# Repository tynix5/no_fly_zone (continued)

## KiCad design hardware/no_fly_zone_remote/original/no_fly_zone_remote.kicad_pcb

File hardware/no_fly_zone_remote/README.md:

# no_fly_zone_remote Schematic + PCB
## Overview

In order to effectively control the quadcopter, the wireless remote control requires several components...

### Microcontroller
The STM32L432KC microcontroller was chosen for its small package, low power draw, and adequate maximum clock speed.
### Control Inputs - Joysticks, Encoders
The joysticks, PS5 TMR (Tunnel Magnetoresistance), were chosen due to their low deadzones, small footprint, and wide availability. The joysticks control the quadcopters throttle, yaw, pitch, and roll. The encoder included on the PCB is used to switch between various menus, displayed on the SSD1306 OLED, and for tuning quadcopter PID parameters easily. 
### Wireless Communication
The nRF24L01 radio was chosen for its availablity and simplicity. For additional improvements, an PA + LNA combo can be added to extend range.
### Charging Circuitry
The charging circuity involves an autoswitching power multiplexer and a linear 1S LiPo charger. The autoswitcher IC automatically chooses the highest available power source. If only LiPo is connected, it is used to power the remote, but if LiPo and USB power are present, USB power is used to power the board and simultaneously charge the LiPo. The board can also be powered using only USB without a LiPo.
### OLED
Displays all relevant information: battery percentages (for both remote and quadcopter), joystick deadzones, PID parameters. Page switches via encoder.
\
\
\
More details are given on the schematics for exact component parameters.\
All footprints and schematics symbols were found online or in KiCAD libraries.

## Versions
The folder structure indicates there are two versions of the PCB: original and revised. The original PCB was never manufactured and used the wrong footprints for several parts, as well as did not have great PCB design characteristics. Instead, the revised version was manufactured and shows all correct footprints and better PCB design methodology. 

An important note on the revised version is Revision 1.0 used the wrong TVS diodes for USB D+ and D-, but these were changed to dedicated USB TVS diodes in a later revision.

## Schematics

### Hierarchal Schematic
The hierarchal schematic details how the MCU, sensors, and power schematics are connected.
<p align="center">
  <br>
</p>

### MCU
<p align="center">
  <br>
</p>

### Sensors (Radio, OLED, Joysticks, Encoder)
<p align="center">
  <br>
</p>

### Misc
Contains four M3 screws with pads, not shown for brevity

### PCB
Note on radio layout: the nRF24L01 is surrounded by a continuous ground plane on the top layer as well as the layer directly underneath the antenna for stability. Stitching vias are placed about ~6mm apart (between lambda/10 - lambda/20 of 2.4 GHz wavelength) near antenna for shielding.
<p align="center">
  <br>
</p>

### 3D Model

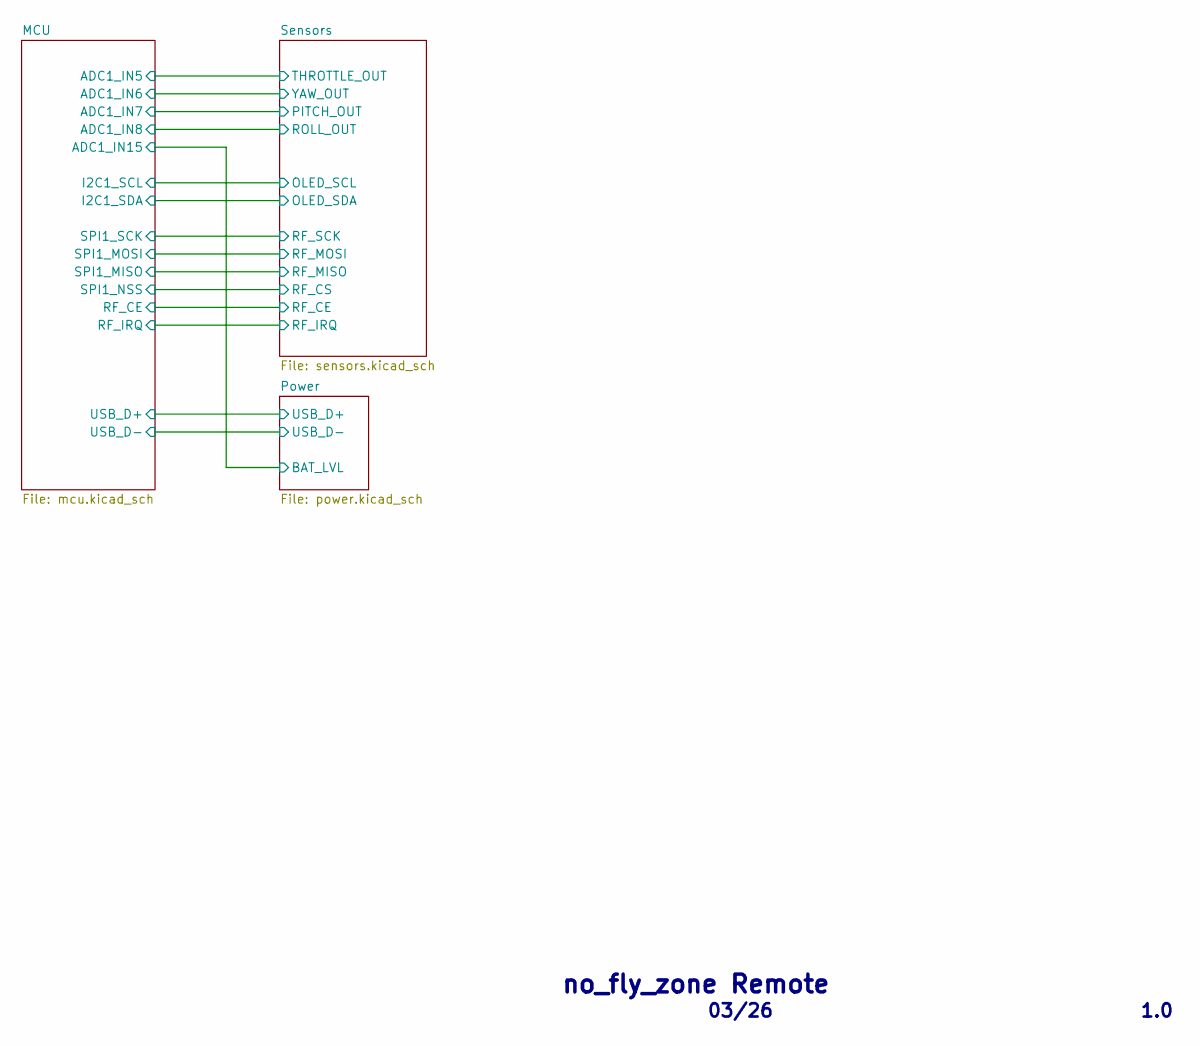
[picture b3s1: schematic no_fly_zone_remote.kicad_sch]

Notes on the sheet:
no_fly_zone Remote
03/26
1.0

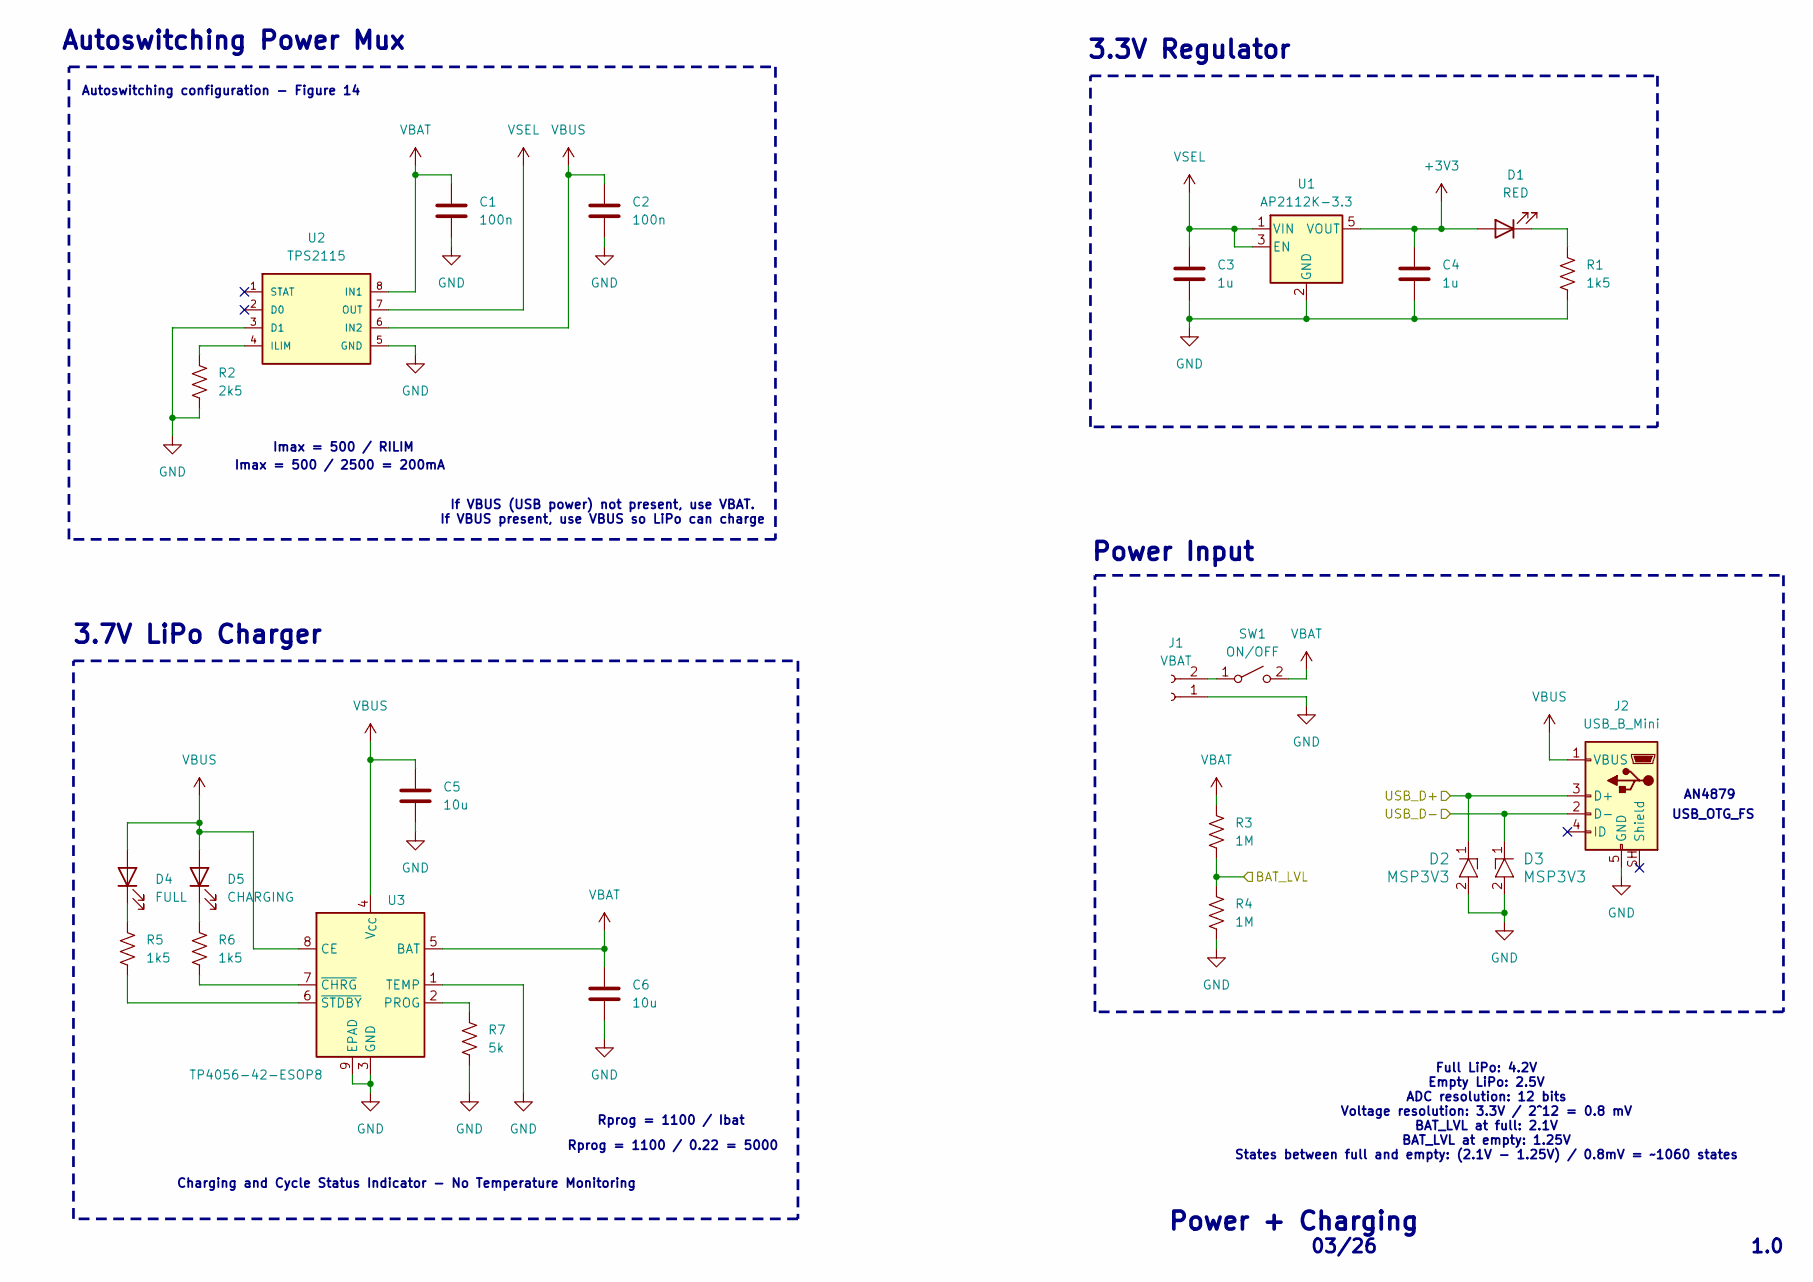
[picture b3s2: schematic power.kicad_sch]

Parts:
C1, C2: 100n; C_0805_2012Metric
C3, C4: 1u; C_0805_2012Metric
C5, C6: 10u; C_0805_2012Metric
D1: RED; LED_0805_2012Metric
D2, D3: MSP3V3; DO-219AD_VIS
D4: FULL; LED_0805_2012Metric
D5: CHARGING; LED_0805_2012Metric
J1: VBAT; JST_PH_S2B-PH-K_1x02_P2.00mm_Horizontal
J2: USB_B_Mini; EDAC_690-005-299-043
R1, R5, R6: 1k5; R_0805_2012Metric
R2: 2k5; R_0805_2012Metric
R3, R4: 1M; R_0805_2012Metric
R7: 5k; R_0805_2012Metric
SW1: ON/OFF; PinHeader_1x02_P2.54mm_Vertical
U1: AP2112K-3.3; SOT-23-5
U2: TPS2115; TPS2115A-TSSOP-8
U3: TP4056-42-ESOP8; SOIC-8-1EP_3.9x4.9mm_P1.27mm_EP2.41x3.3mm

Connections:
+3V3: C4.1, D1.2 (A), U1.5 (VOUT); also elsewhere on the board
/MCU/ADC1_IN15: R3.2, R4.1; also elsewhere on the board
/MCU/USB_D+: D2.1, J2.3 (D+); also elsewhere on the board
/MCU/USB_D-: D3.1, J2.2 (D-); also elsewhere on the board
GND: C1.2, C2.2, C3.2, C4.2, C5.2, C6.2, D2.2, D3.2, J1.1, J2.5 (GND), R1.2, R2.2, R4.2, R7.2, U1.2 (GND), U2.3 (D1), U2.5 (GND), U3.1 (TEMP), U3.3 (GND), U3.9 (EPAD); also elsewhere on the board
unnamed: D1.1 (K), R1.1
unnamed: D4.1 (K), R5.1
unnamed: D5.1 (K), R6.1
unnamed: J1.2, SW1.1 (A)
unnamed: R2.1, U2.4 (ILIM)
unnamed: R7.1, U3.2 (PROG)
unnamed: R6.2, U3.7 (~CHRG)
unnamed: R5.2, U3.6 (~STDBY)
VBAT: C1.1, C6.1, R3.1, SW1.2 (B), U2.8 (IN1), U3.5 (BAT)
VBUS: C2.1, C5.1, D4.2 (A), D5.2 (A), J2.1 (VBUS), U2.6 (IN2), U3.4 (V_{CC}), U3.8 (CE)
VSEL: C3.1, U1.1 (VIN), U1.3 (EN), U2.7 (OUT)

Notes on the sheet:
Power + Charging
Power Input
3.3V Regulator
Rprog = 1100 / 0.22 = 5000
Imax = 500 / 2500 = 200mA
1.0
Rprog = 1100 / Ibat
Imax = 500 / RILIM
Autoswitching Power Mux
If VBUS (USB power) not present, use VBAT. If VBUS present, use VBUS so LiPo can charge
03/26
Autoswitching configuration - Figure 14
3.7V LiPo Charger
Charging and Cycle Status Indicator - No Temperature Monitoring
USB_OTG_FS
AN4879
Full LiPo: 4.2V Empty LiPo: 2.5V ADC resolution: 12 bits Voltage resolution: 3.3V / 2^12 = 0.8 mV BAT_LVL at full: 2.1V BAT_LVL at empty: 1.25V States between full and empty: (2.1V - 1.25V) / 0.8mV = ~1060 states

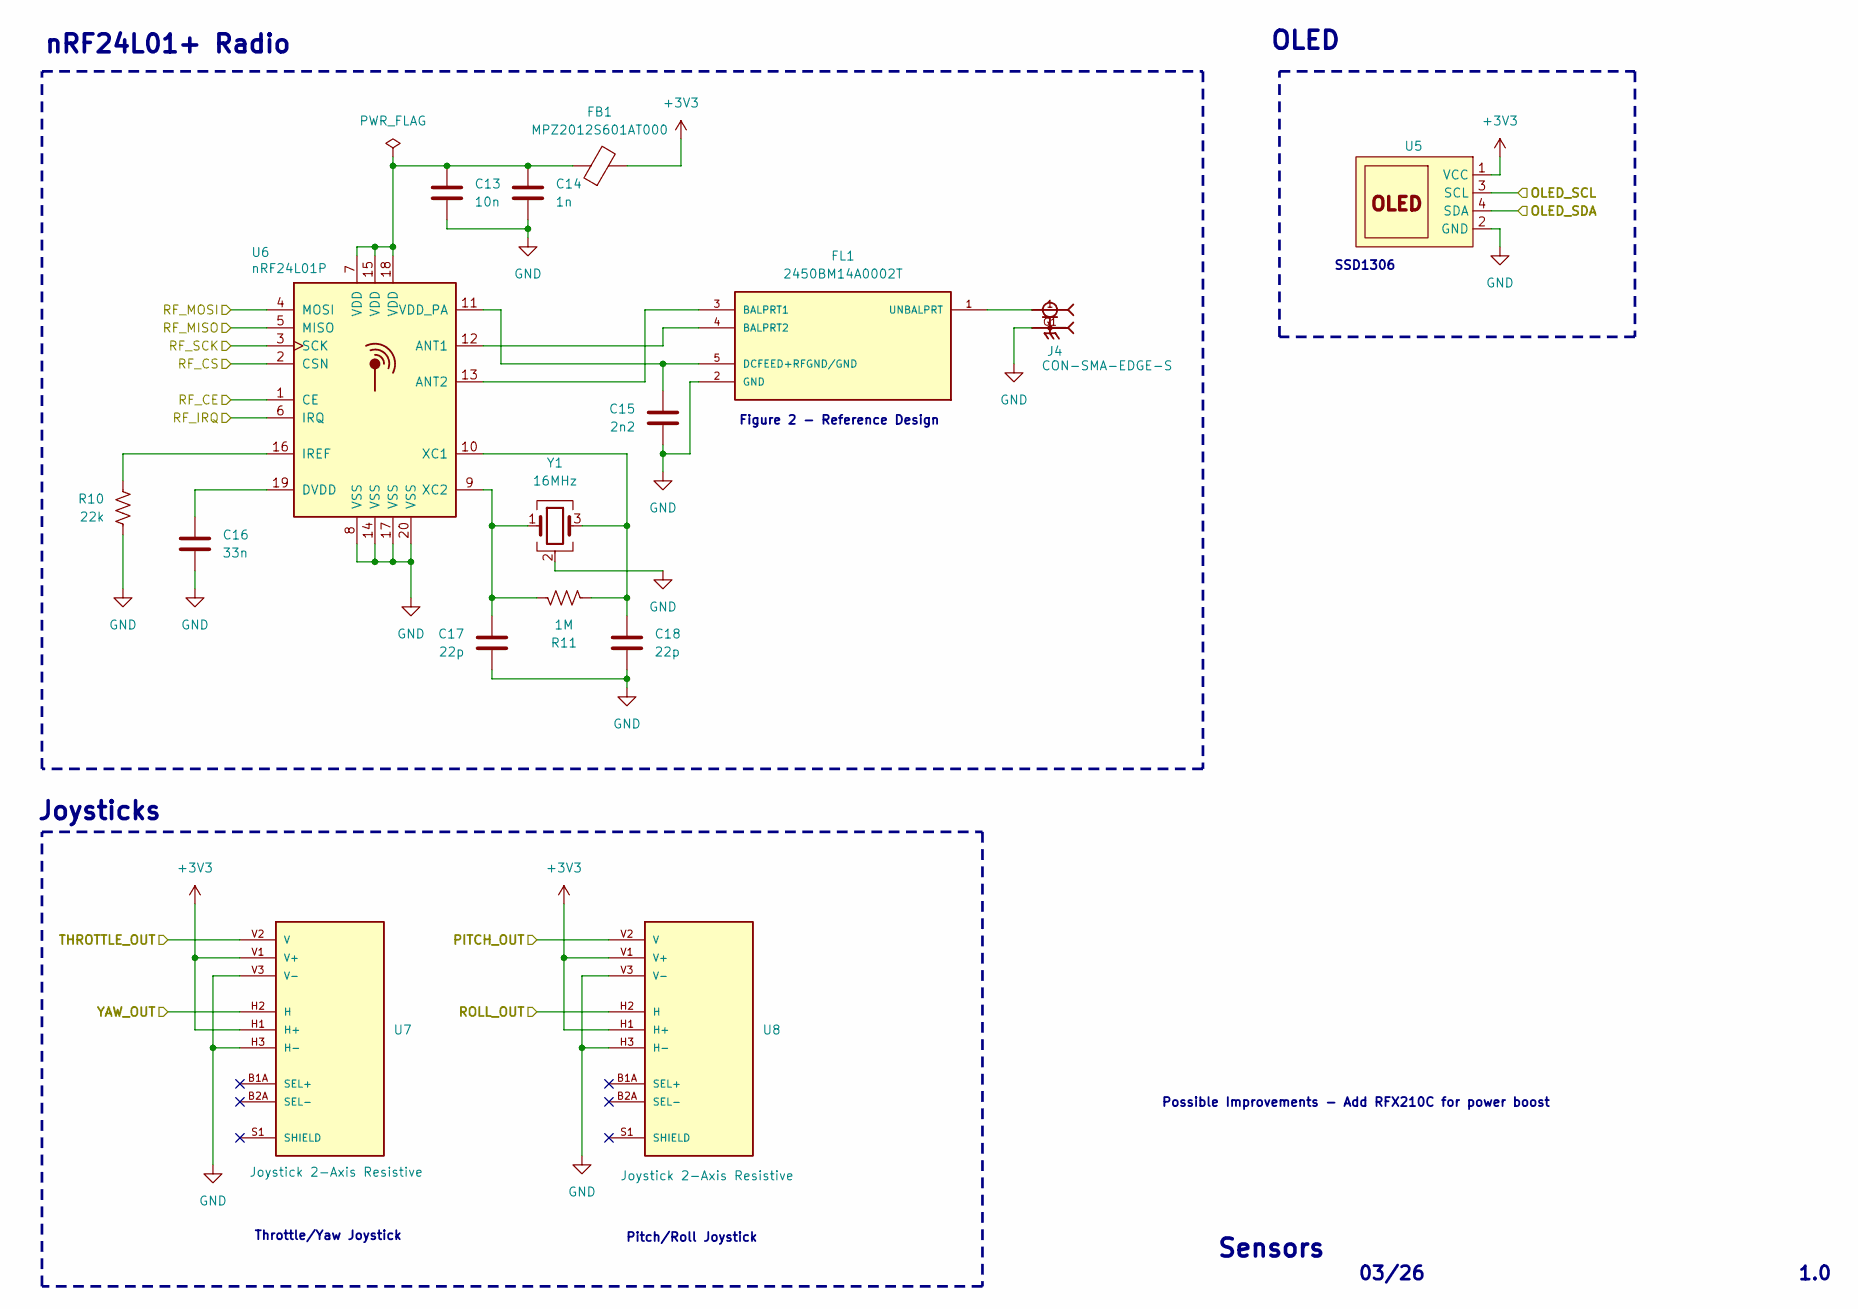
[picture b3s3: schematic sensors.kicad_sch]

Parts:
C13: 10n; C_0402_1005Metric
C14: 1n; C_0402_1005Metric
C15: 2n2; C_0402_1005Metric
C16: 33n; C_0402_1005Metric
C17, C18: 22p; C_0402_1005Metric
FB1: MPZ2012S601AT000; R_0805_2012Metric
FL1: 2450BM14A0002T; FIL_2450BM14A0002T
J4: CON-SMA-EDGE-S; RFSOLUTIONS_CON-SMA-EDGE-S
R10: 22k; R_0402_1005Metric
R11: 1M; R_0402_1005Metric
U5: PinHeader_1x04_P2.54mm_Vertical
U6: nRF24L01P; QFN-20-1EP_4x4mm_P0.5mm_EP2.5x2.5mm
U7, U8: Joystick 2-Axis Resistive; XDCR_COM-09032
Y1: 16MHz; XTAL_ABM8AIG-16.000MHZ-12-2Z-T3

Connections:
+3V3: FB1.2, U5.1 (VCC), U7.H1 (H+), U7.V1 (V+), U8.H1 (H+), U8.V1 (V+); also elsewhere on the board
/MCU/ADC1_IN5: U7.V2 (V); also elsewhere on the board
/MCU/ADC1_IN6: U7.H2 (H); also elsewhere on the board
/MCU/ADC1_IN7: U8.V2 (V); also elsewhere on the board
/MCU/ADC1_IN8: U8.H2 (H); also elsewhere on the board
/MCU/I2C1_SCL: U5.3 (SCL); also elsewhere on the board
/MCU/I2C1_SDA: U5.4 (SDA); also elsewhere on the board
/MCU/RF_CE: U6.1 (CE); also elsewhere on the board
/MCU/RF_IRQ: U6.6 (IRQ); also elsewhere on the board
/MCU/SPI1_MISO: U6.5 (MISO); also elsewhere on the board
/MCU/SPI1_MOSI: U6.4 (MOSI); also elsewhere on the board
/MCU/SPI1_NSS: U6.2 (CSN); also elsewhere on the board
/MCU/SPI1_SCK: U6.3 (SCK); also elsewhere on the board
GND: C13.2, C14.2, C15.2, C16.2, C17.2, C18.2, FL1.2 (GND), J4.G1, J4.G2, J4.G3, J4.G4, R10.2, U5.2 (GND), U6.8 (VSS), U6.14 (VSS), U6.17 (VSS), U6.20 (VSS), U7.H3 (H-), U7.V3 (V-), U8.H3 (H-), U8.V3 (V-), Y1.2 (G), Y1.4 (G); also elsewhere on the board
unnamed: C13.1, C14.1, FB1.1, U6.7 (VDD), U6.15 (VDD), U6.18 (VDD)
unnamed: FL1.3 (BALPRT1), U6.13 (ANT2)
unnamed: FL1.4 (BALPRT2), U6.12 (ANT1)
unnamed: C15.1, FL1.5 (DCFEED+RFGND/GND), U6.11 (VDD_PA)
unnamed: FL1.1 (UNBALPRT), J4.1
unnamed: C16.1, U6.19 (DVDD)
unnamed: R10.1, U6.16 (IREF)
unnamed: C18.1, R11.1, U6.10 (XC1), Y1.3
unnamed: C17.1, R11.2, U6.9 (XC2), Y1.1

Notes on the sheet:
03/26
Figure 2 - Reference Design
nRF24L01+ Radio
SSD1306
Joysticks
OLED
1.0
Sensors
Throttle/Yaw Joystick
Pitch/Roll Joystick
Possible Improvements - Add RFX210C for power boost

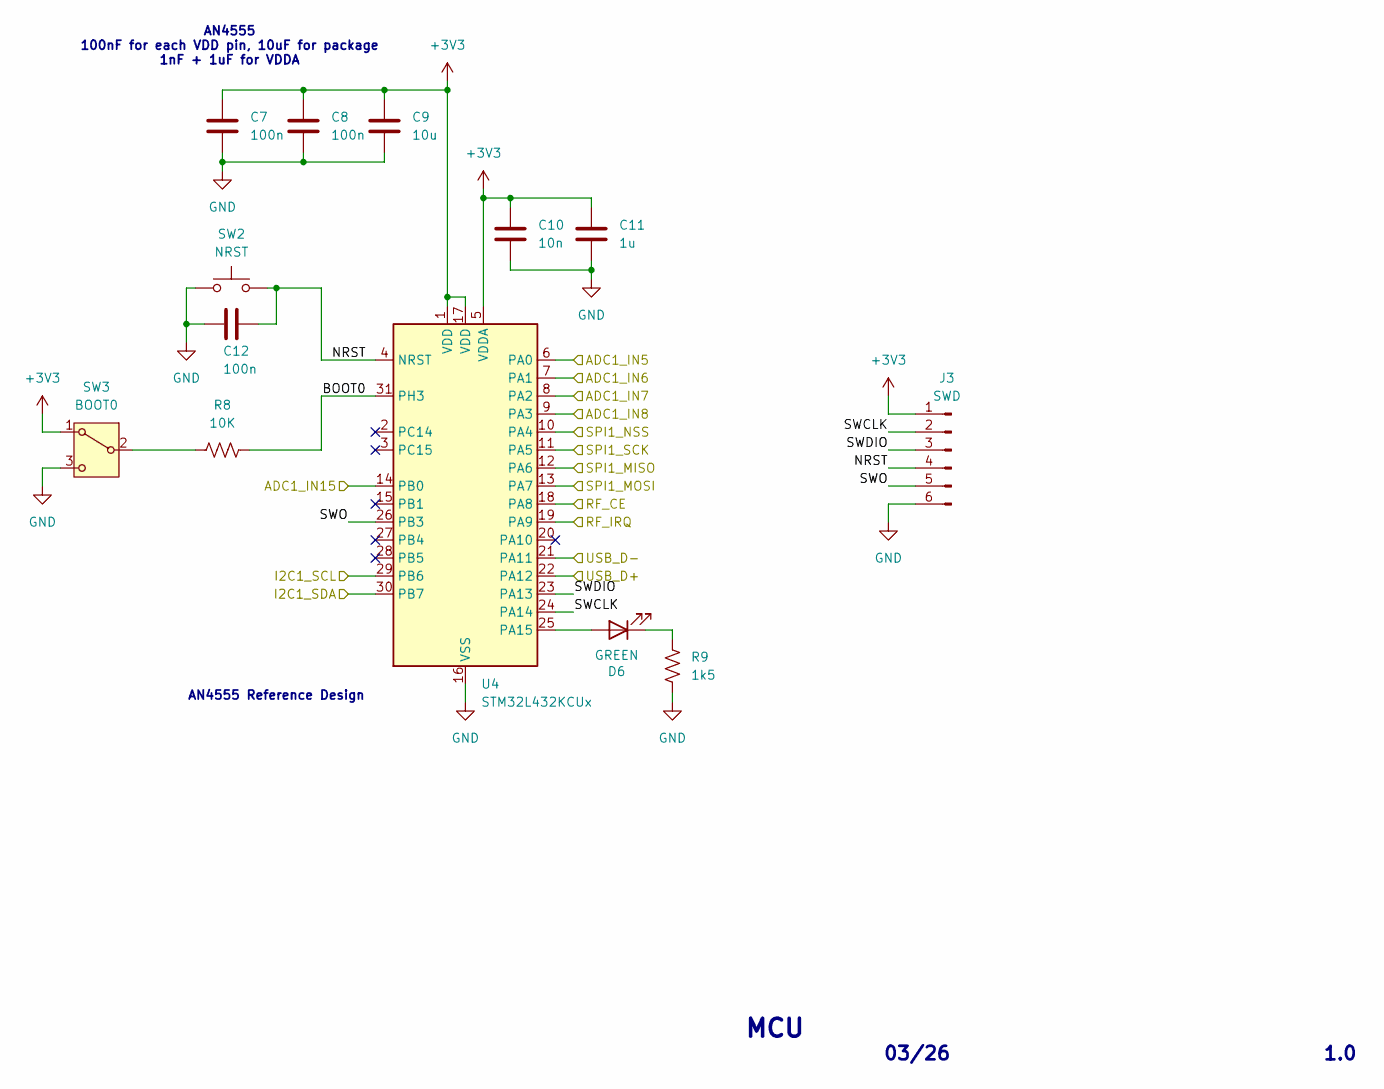
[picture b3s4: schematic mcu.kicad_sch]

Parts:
C7, C8, C12: 100n; C_0805_2012Metric
C9: 10u; C_0805_2012Metric
C10: 10n; C_0805_2012Metric
C11: 1u; C_0805_2012Metric
D6: GREEN; LED_0805_2012Metric
J3: SWD; PinHeader_1x06_P2.54mm_Vertical
R8: 10K; R_0805_2012Metric
R9: 1k5; R_0805_2012Metric
SW2: NRST; SW_SPST_TL3305A
SW3: BOOT0; SW_SPDT_PCM12
U4: STM32L432KCUx; QFN-32-1EP_5x5mm_P0.5mm_EP3.45x3.45mm

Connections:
+3V3: C7.1, C8.1, C9.1, C10.1, C11.1, J3.1, SW3.1 (A), U4.1 (VDD), U4.5 (VDDA), U4.17 (VDD); also elsewhere on the board
/MCU/ADC1_IN5: U4.6 (PA0); also elsewhere on the board
/MCU/ADC1_IN6: U4.7 (PA1); also elsewhere on the board
/MCU/ADC1_IN7: U4.8 (PA2); also elsewhere on the board
/MCU/ADC1_IN8: U4.9 (PA3); also elsewhere on the board
/MCU/ADC1_IN15: U4.14 (PB0); also elsewhere on the board
/MCU/BOOT0: R8.2, U4.31 (PH3)
/MCU/I2C1_SCL: U4.29 (PB6); also elsewhere on the board
/MCU/I2C1_SDA: U4.30 (PB7); also elsewhere on the board
/MCU/NRST: C12.1, J3.4, SW2.2, U4.4 (NRST)
/MCU/RF_CE: U4.18 (PA8); also elsewhere on the board
/MCU/RF_IRQ: U4.19 (PA9); also elsewhere on the board
/MCU/SPI1_MISO: U4.12 (PA6); also elsewhere on the board
/MCU/SPI1_MOSI: U4.13 (PA7); also elsewhere on the board
/MCU/SPI1_NSS: U4.10 (PA4); also elsewhere on the board
/MCU/SPI1_SCK: U4.11 (PA5); also elsewhere on the board
/MCU/SWCLK: J3.2, U4.24 (PA14)
/MCU/SWDIO: J3.3, U4.23 (PA13)
/MCU/SWO: J3.5, U4.26 (PB3)
/MCU/USB_D+: U4.22 (PA12); also elsewhere on the board
/MCU/USB_D-: U4.21 (PA11); also elsewhere on the board
GND: C7.2, C8.2, C9.2, C10.2, C11.2, C12.2, J3.6, R9.2, SW2.1, SW3.3 (C), U4.16 (VSS), U4.32 (VSS), U4.33 (VSS); also elsewhere on the board
unnamed: D6.2 (A), U4.25 (PA15)
unnamed: D6.1 (K), R9.1
unnamed: R8.1, SW3.2 (B)

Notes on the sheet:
03/26
AN4555 Reference Design
AN4555 100nF for each VDD pin, 10uF for package 1nF + 1uF for VDDA
MCU
1.0

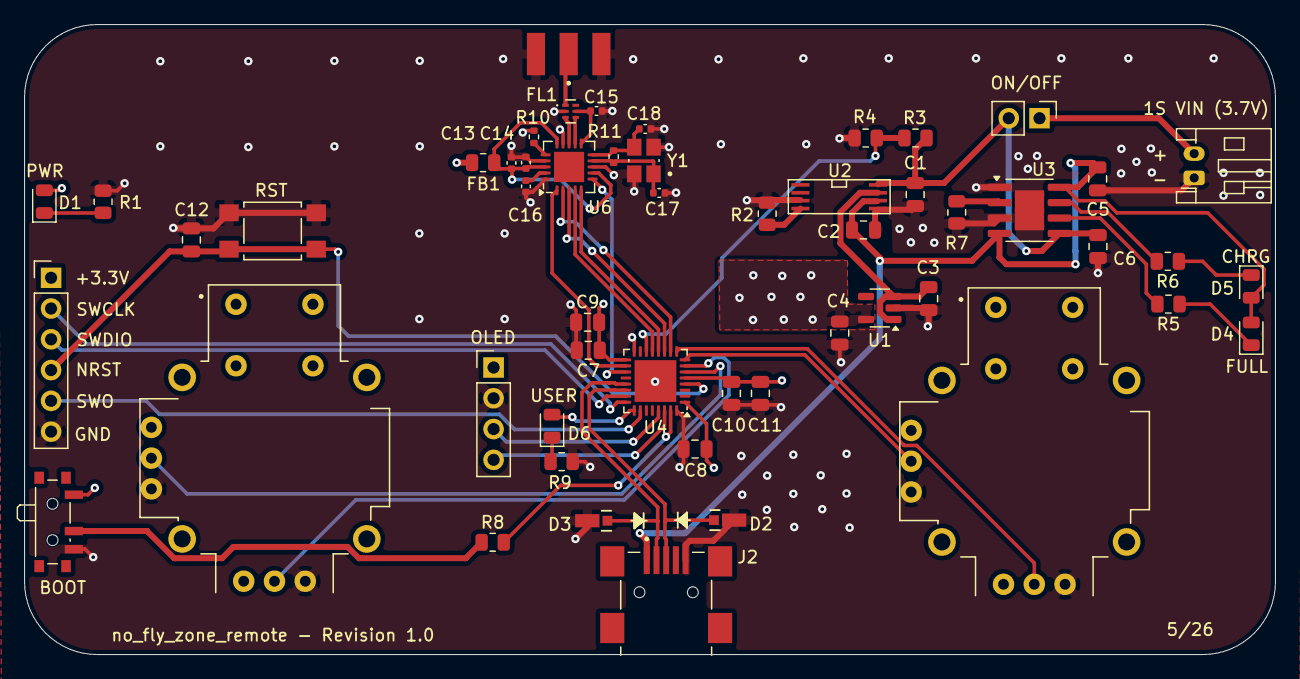
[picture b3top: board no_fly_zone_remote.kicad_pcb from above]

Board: 4 copper layers, 103.2 x 52.0 mm, 53 parts (0 on the bottom side), 45 nets.

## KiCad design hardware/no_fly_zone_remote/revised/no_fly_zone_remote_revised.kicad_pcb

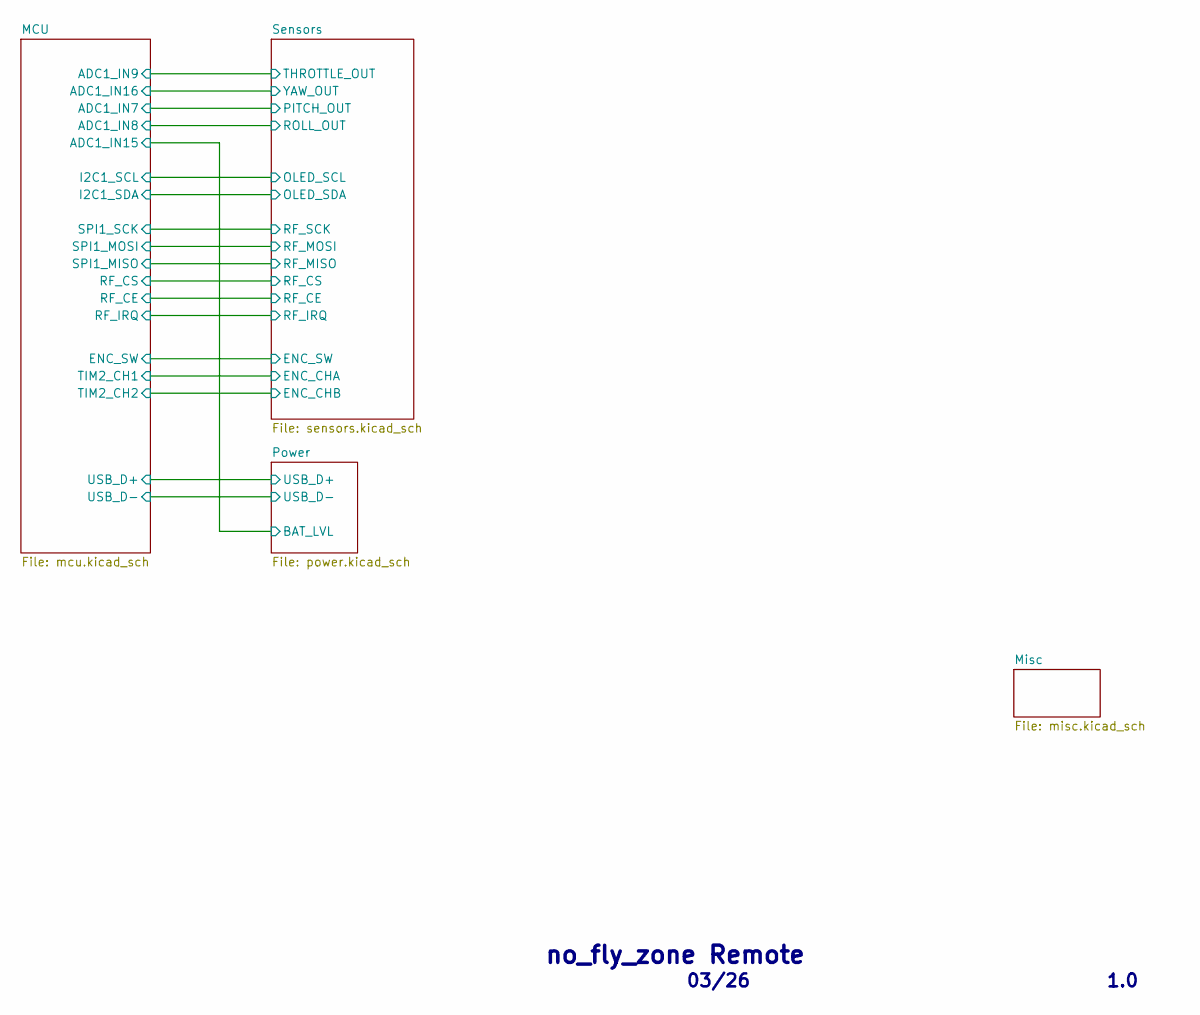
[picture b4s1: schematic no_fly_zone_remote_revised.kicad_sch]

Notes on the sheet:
no_fly_zone Remote
03/26
1.0

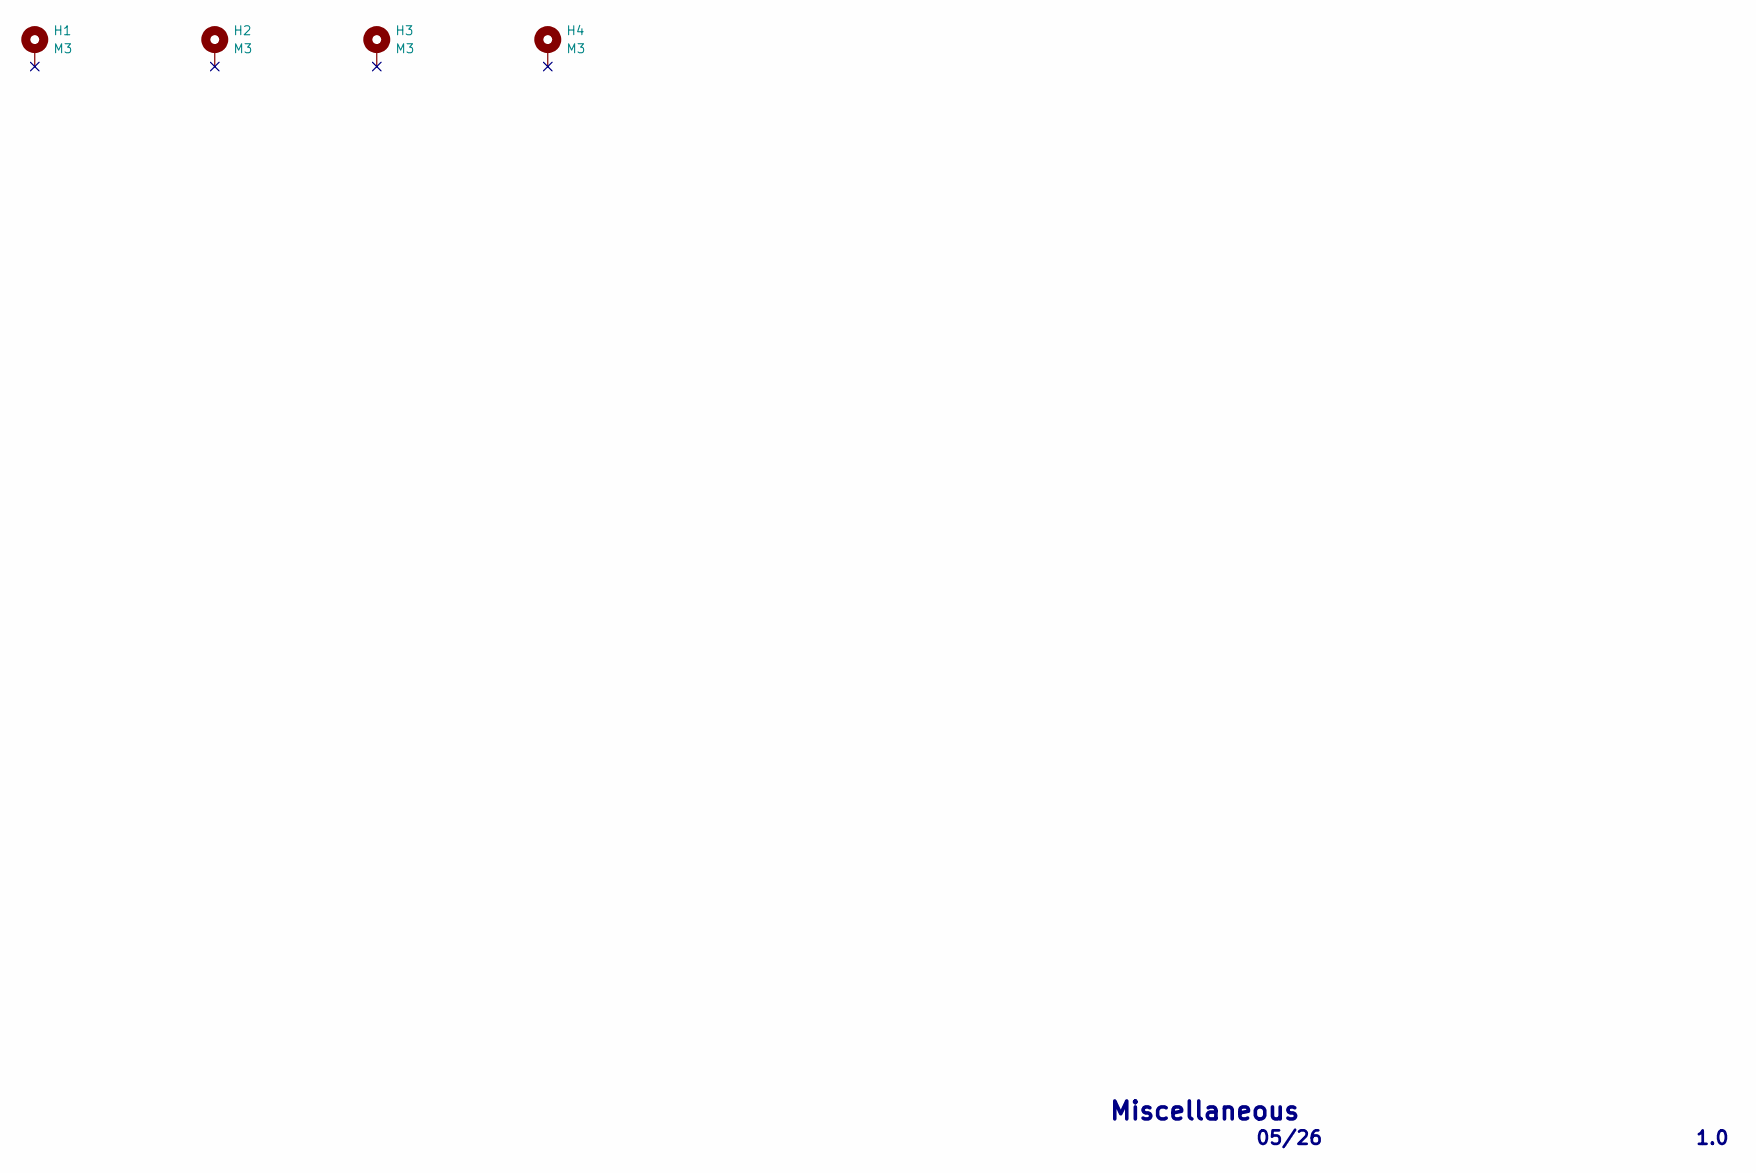
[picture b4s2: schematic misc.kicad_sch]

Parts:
H1, H2, H3, H4: M3; MountingHole_3.2mm_M3_Pad

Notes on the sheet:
1.0
05/26
Miscellaneous

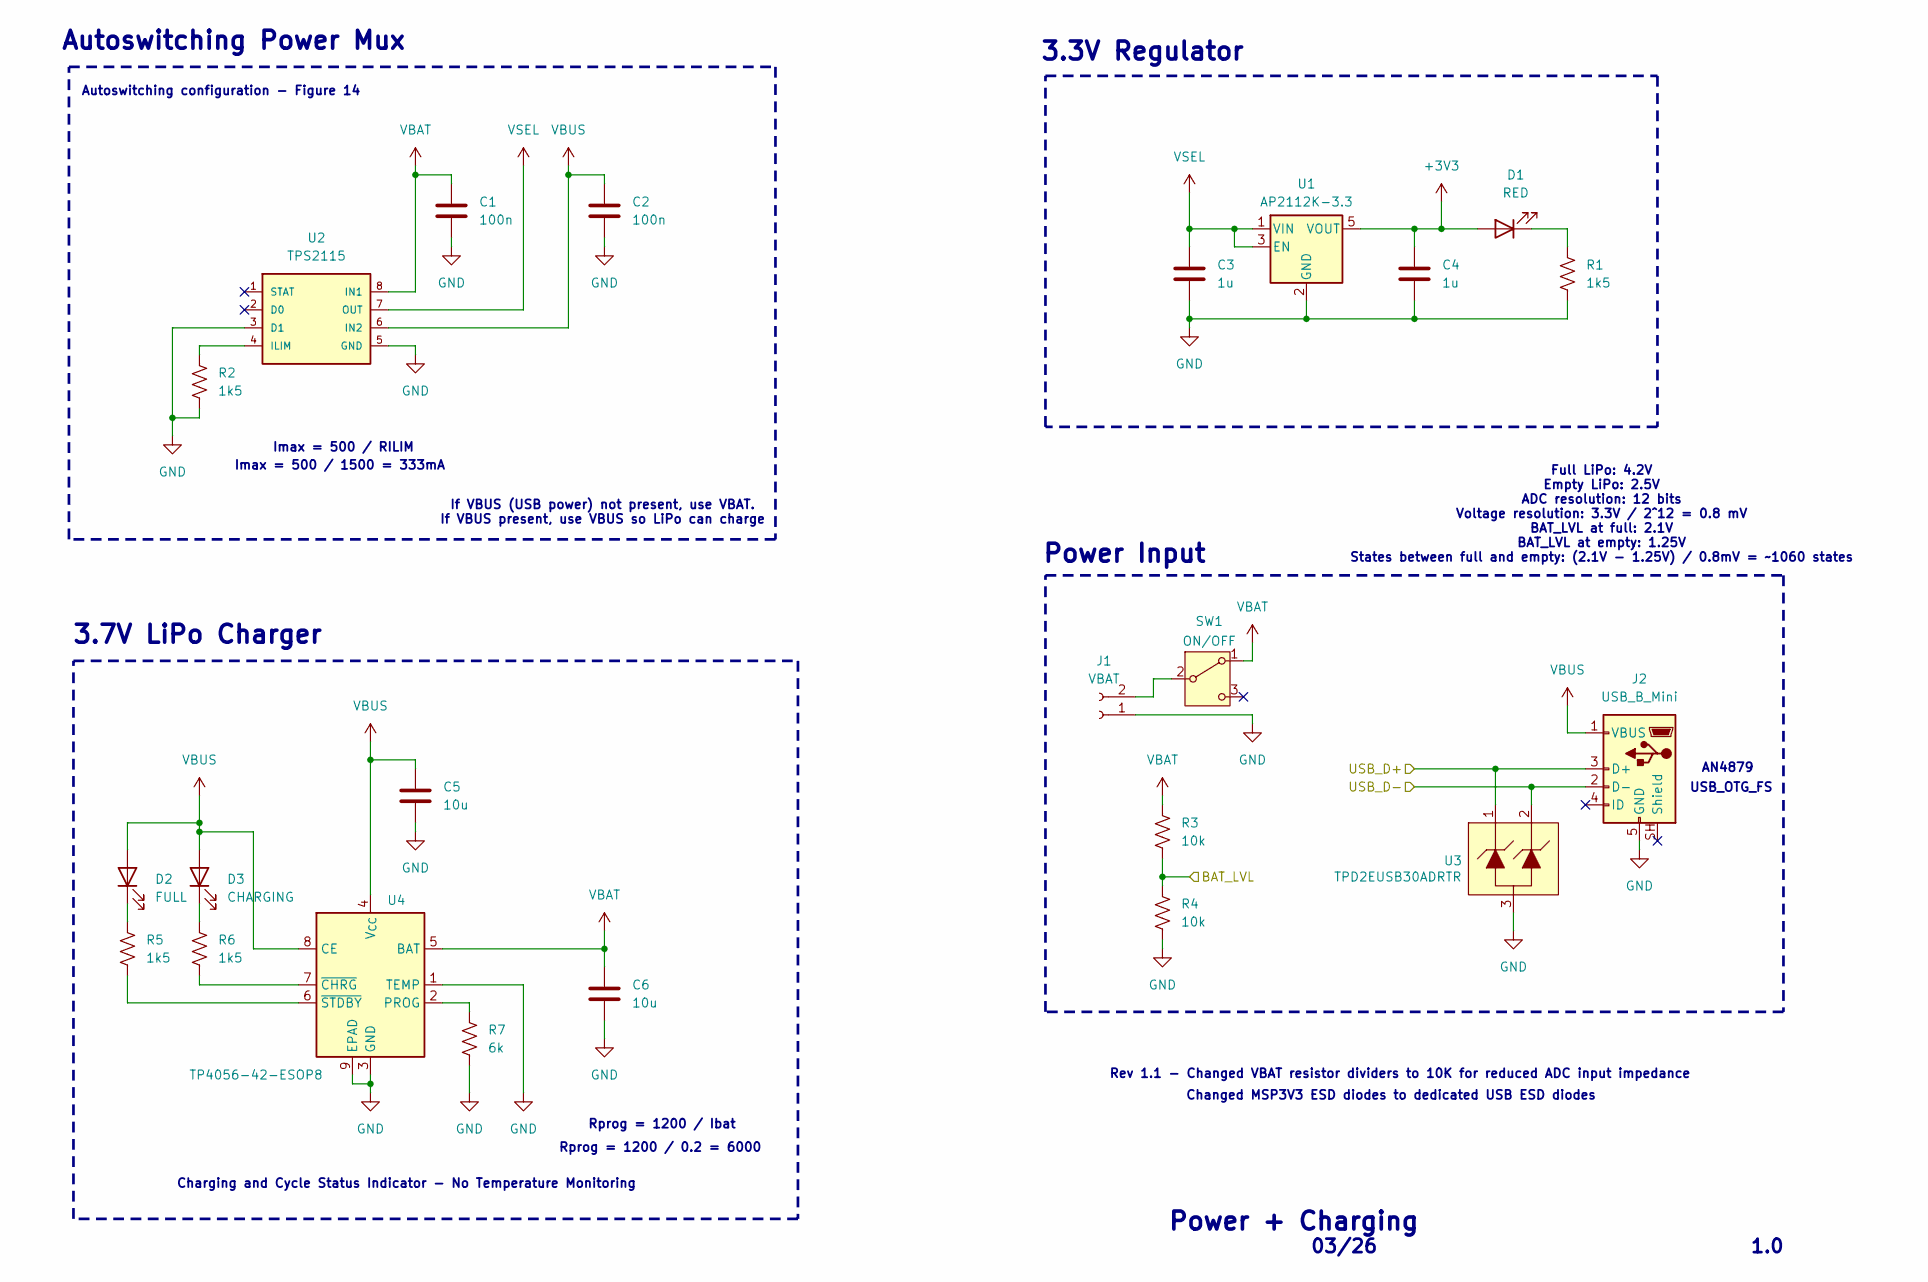
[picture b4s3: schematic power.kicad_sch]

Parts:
C1, C2: 100n; C_0805_2012Metric
C3, C4: 1u; C_0805_2012Metric
C5, C6: 10u; C_0805_2012Metric
D1: RED; LED_0805_2012Metric
D2: FULL; LED_0805_2012Metric
D3: CHARGING; LED_0805_2012Metric
J1: VBAT; JST_PH_S2B-PH-K_1x02_P2.00mm_Horizontal
J2: USB_B_Mini; EDAC_690-005-299-043
R1, R2, R5, R6: 1k5; R_0805_2012Metric
R3, R4: 10k; R_0805_2012Metric
R7: 6k; R_0805_2012Metric
SW1: ON/OFF; SW_SPDT_PCM12
U1: AP2112K-3.3; SOT-23-5
U2: TPS2115; TPS2115A-TSSOP-8
U3: SOT-723
U4: TP4056-42-ESOP8; SOIC-8-1EP_3.9x4.9mm_P1.27mm_EP2.41x3.3mm

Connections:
+3V3: C4.1, D1.2 (A), U1.5 (VOUT); also elsewhere on the board
/MCU/ADC1_IN15: R3.2, R4.1; also elsewhere on the board
/MCU/USB_D+: J2.3 (D+), U3.1; also elsewhere on the board
/MCU/USB_D-: J2.2 (D-), U3.2; also elsewhere on the board
GND: C1.2, C2.2, C3.2, C4.2, C5.2, C6.2, J1.1, J2.5 (GND), R1.2, R2.2, R4.2, R7.2, U1.2 (GND), U2.3 (D1), U2.5 (GND), U3.3, U4.1 (TEMP), U4.3 (GND), U4.9 (EPAD); also elsewhere on the board
unnamed: D1.1 (K), R1.1
unnamed: D2.1 (K), R5.1
unnamed: D3.1 (K), R6.1
unnamed: J1.2, SW1.2 (B)
unnamed: R2.1, U2.4 (ILIM)
unnamed: R7.1, U4.2 (PROG)
unnamed: R6.2, U4.7 (~CHRG)
unnamed: R5.2, U4.6 (~STDBY)
VBAT: C1.1, C6.1, R3.1, SW1.1 (A), U2.8 (IN1), U4.5 (BAT)
VBUS: C2.1, C5.1, D2.2 (A), D3.2 (A), J2.1 (VBUS), U2.6 (IN2), U4.4 (V_{CC}), U4.8 (CE)
VSEL: C3.1, U1.1 (VIN), U1.3 (EN), U2.7 (OUT)

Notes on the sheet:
Power + Charging
Power Input
3.3V Regulator
Rprog = 1200 / 0.2 = 6000
Imax = 500 / 1500 = 333mA
1.0
Rprog = 1200 / Ibat
Imax = 500 / RILIM
Autoswitching Power Mux
If VBUS (USB power) not present, use VBAT. If VBUS present, use VBUS so LiPo can charge
03/26
Autoswitching configuration - Figure 14
Rev 1.1 - Changed VBAT resistor dividers to 10K for reduced ADC input impedance
3.7V LiPo Charger
Charging and Cycle Status Indicator - No Temperature Monitoring
Changed MSP3V3 ESD diodes to dedicated USB ESD diodes
USB_OTG_FS
AN4879
Full LiPo: 4.2V Empty LiPo: 2.5V ADC resolution: 12 bits Voltage resolution: 3.3V / 2^12 = 0.8 mV BAT_LVL at full: 2.1V BAT_LVL at empty: 1.25V States between full and empty: (2.1V - 1.25V) / 0.8mV = ~1060 states
